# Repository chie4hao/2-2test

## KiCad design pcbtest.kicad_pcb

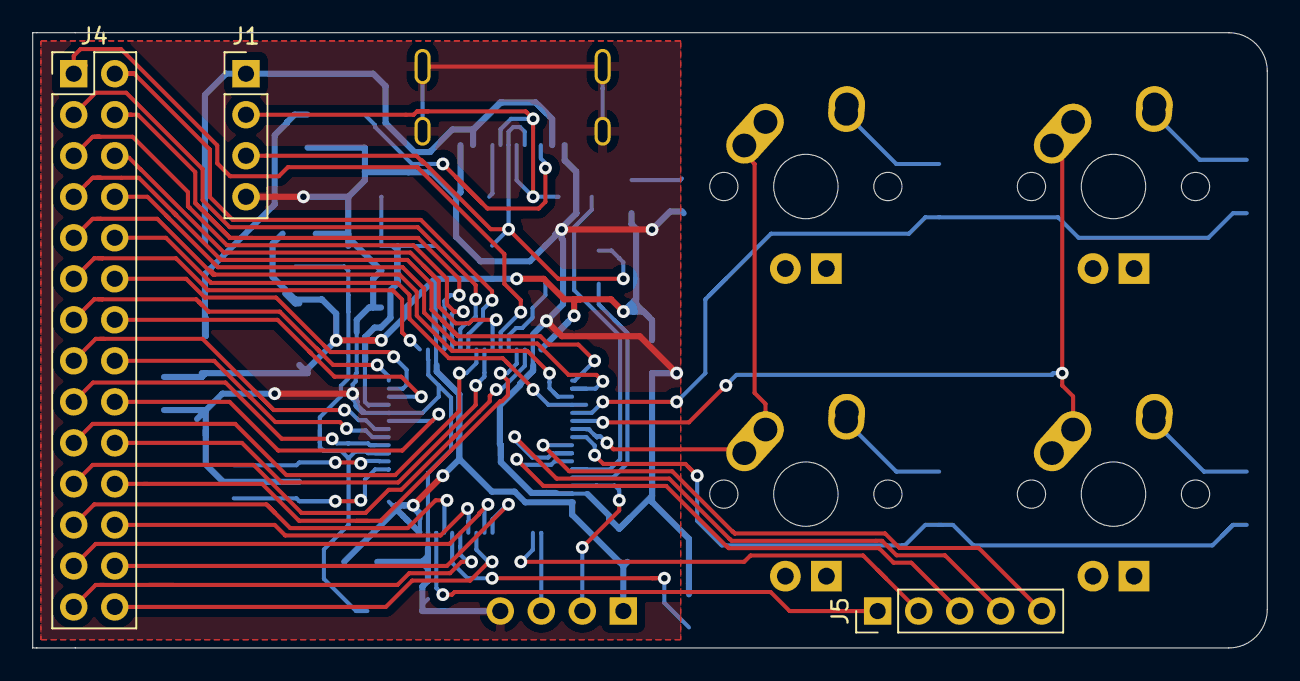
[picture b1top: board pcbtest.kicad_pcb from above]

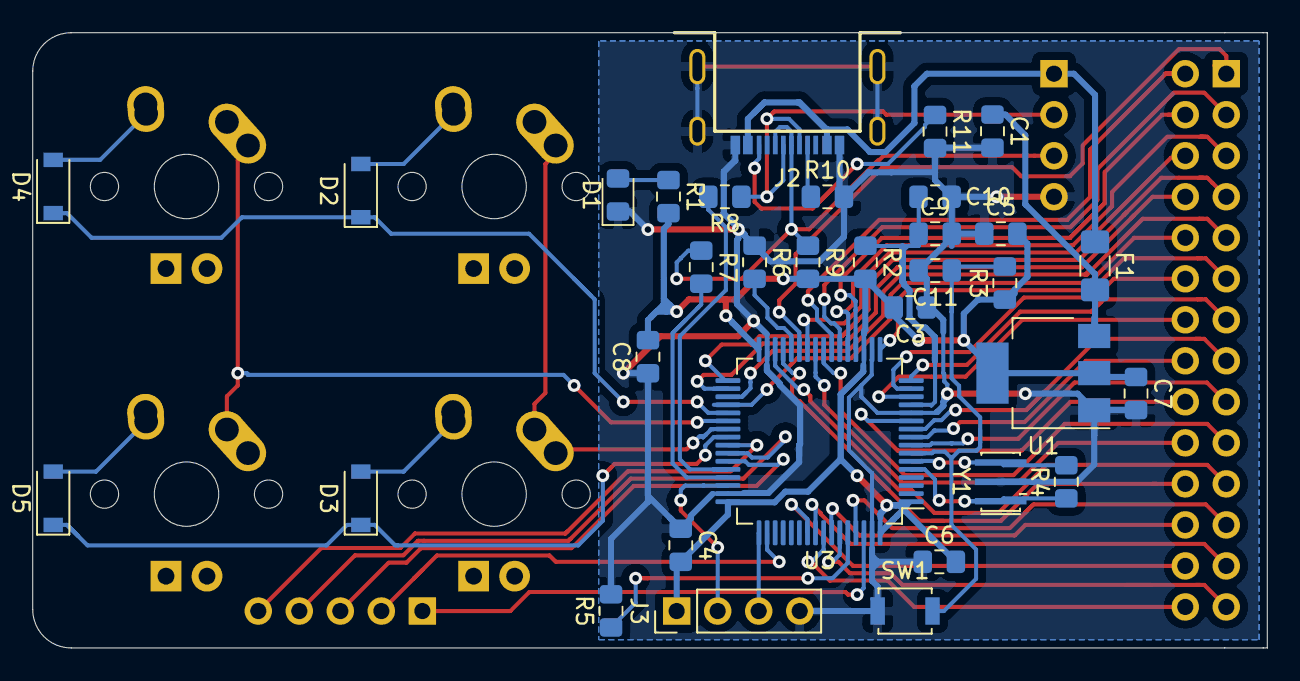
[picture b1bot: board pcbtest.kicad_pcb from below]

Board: 2 copper layers, 76.5 x 38.1 mm, 40 parts (33 on the bottom side), 60 nets.

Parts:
C1, C7, C9: 106; C_0805_2012Metric_Pad1.15x1.40mm_HandSolder
C3, C4, C5, C6, C8, C10, C11: 104; C_0805_2012Metric_Pad1.15x1.40mm_HandSolder
D1: LED; LED_0805_2012Metric_Pad1.15x1.40mm_HandSolder
D2, D3, D4, D5: sod-123; D_SOD-123
F1: 500mA; Fuse_1206_3216Metric_Pad1.42x1.75mm_HandSolder
J1: usb2.0; PinHeader_1x04_P2.54mm_Vertical
J2: USB_C_USB2.0; USB-C-12-Pin-MidMount
J3: SWD; PinHeader_1x04_P2.54mm_Vertical
J4: 28pinheader; PinHeader_2x14_P2.54mm_Vertical
J5: 5pinheader; PinHeader_1x05_P2.54mm_Vertical
MX1, MX2, MX3, MX4: MX-1U
R1: 1k; R_0805_2012Metric_Pad1.15x1.40mm_HandSolder
R2: 10R; R_0805_2012Metric_Pad1.15x1.40mm_HandSolder
R3, R5, R6: 10k; R_0805_2012Metric_Pad1.15x1.40mm_HandSolder
R4: 1M; R_0805_2012Metric_Pad1.15x1.40mm_HandSolder
R7, R8: 22; R_0805_2012Metric_Pad1.15x1.40mm_HandSolder
R9: 1.5k; R_0805_2012Metric_Pad1.15x1.40mm_HandSolder
R10, R11: 5.1k; R_0805_2012Metric_Pad1.15x1.40mm_HandSolder
SW1: SW_Push; SW_SPST_B3U-1000P
U1: AMS1117-3.3; SOT-223-3_TabPin2
U3: STM32F103RETx; LQFP-64_10x10mm_P0.5mm
Y1: 8M; Resonator_SMD_muRata_CSTxExxV-3Pin_3.0x1.1mm_HandSoldering

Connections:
+3V3: C3.2, C4.2, C5.2, C6.2, C7.1, C8.2, J3.1, R1.2, R2.2, R3.1, R9.2, U1.2, U3.1, U3.19, U3.32, U3.48, U3.64
+5V: C1.1, F1.2, U1.3
/PA0: J4.14, U3.14
/PA1: J4.12, U3.15
/PA2: J4.13, U3.16
/PA3: J4.11, U3.17
/PA4: J4.4, U3.20
/PA5: J4.5, U3.21
/PA6: J4.3, U3.22
/PA7: J4.2, U3.23
/PA8: J5.5, U3.41
/PA15: J5.2, U3.50
/PB0: J4.6, U3.26
/PB1: J4.1, U3.27
/PB3: J4.26, U3.55
/PB4: J4.25, U3.56
/PB5: J4.28, U3.57
/PB6: J4.24, U3.58
/PB7: J4.27, U3.59
/PB8: J4.23, U3.61
/PB9: J5.1, U3.62
/PB10: J4.22, U3.29
/PB11: J4.21, U3.30
/PB12: J4.7, U3.33
/PB13: J4.8, U3.34
/PB14: J4.9, U3.35
/PB15: J4.10, U3.36
/PC0: J4.17, U3.8
/PC1: J4.16, U3.9
/PC2: J4.15, U3.10
/PC3: J4.18, U3.11
/PC4: J4.19, U3.24
/PC5: J4.20, U3.25
COL0: MX1.1, MX2.1, U3.39
COL1: MX3.1, MX4.1, U3.38
GND: C1.2, C3.1, C4.1, C5.1, C6.1, C7.2, C8.1, C9.2, C10.1, C11.2, D1.1, J1.4, J2.1, J2.12, J2.13, J3.4, R5.2, R6.1, R10.2, R11.2, SW1.1, U1.1, U3.12, U3.18, U3.31, U3.47, U3.63, Y1.2
unnamed: C11.1, R3.2, SW1.2, U3.7
unnamed: D1.2, R1.1
unnamed: D2.2, MX1.2
unnamed: D3.2, MX2.2
unnamed: D4.2, MX3.2
unnamed: D5.2, MX4.2
unnamed: J2.4, R10.1
unnamed: J2.10, R11.1
unnamed: R4.1, U3.5, Y1.1
unnamed: R4.2, U3.6, Y1.3
unnamed: R5.1, U3.60
unnamed: R6.2, U3.28
unnamed: R7.2, U3.45
unnamed: R8.2, U3.44
ROW0: D2.1, D4.1, U3.37
ROW1: D3.1, D5.1, U3.40
RXD: J5.3, U3.43
SWCLK: J3.3, U3.49
SWDIO: J3.2, U3.46
TXD: J5.4, U3.42
USB_D+: J1.3, J2.6, J2.8, R7.1, R9.1
USB_D-: J1.2, J2.5, J2.7, R8.1
VCC: F1.1, J1.1, J2.2, J2.11
VDDA: C9.1, C10.2, R2.1, U3.13

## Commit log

2019-05-16 add new file
